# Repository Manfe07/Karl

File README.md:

# Karl
ROS based Raspberry Pi Robot with LIDAR

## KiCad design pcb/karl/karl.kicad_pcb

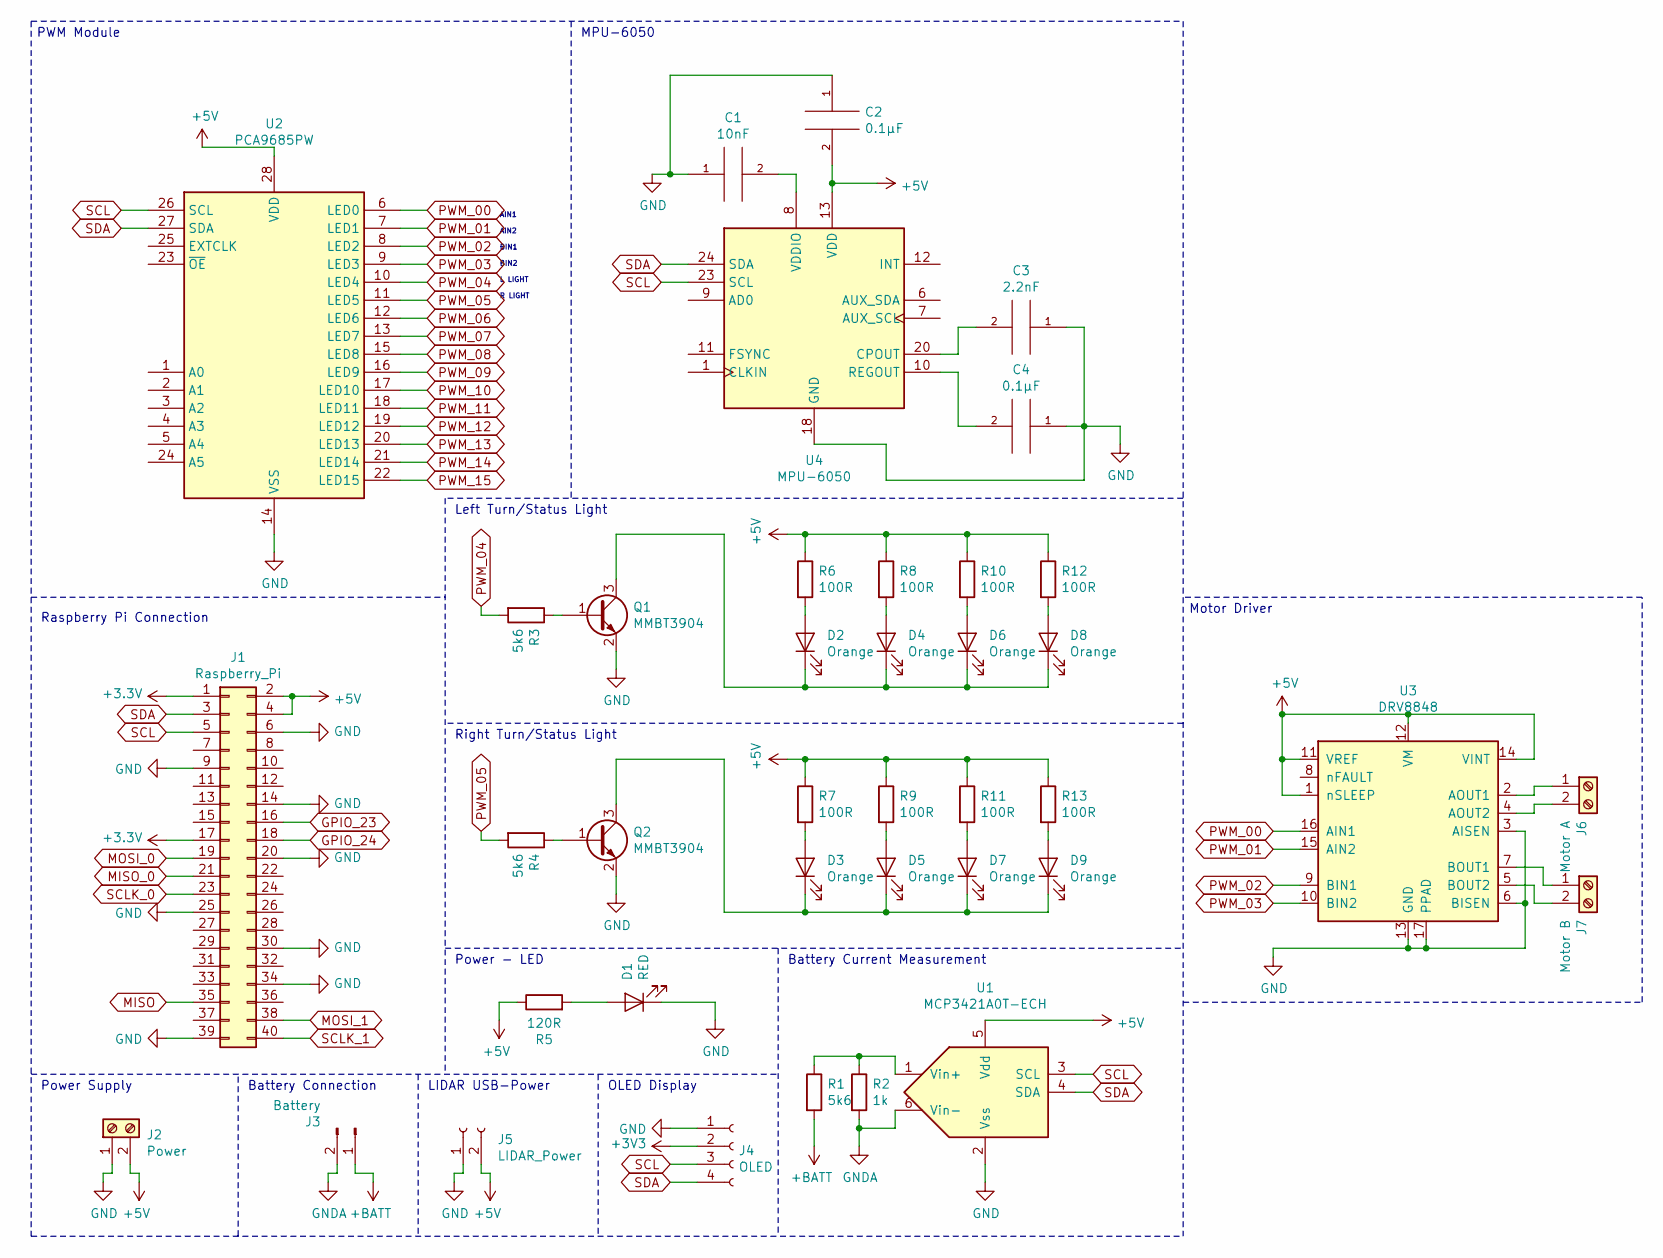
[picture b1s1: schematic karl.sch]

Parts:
C1: 10nF; C_0201_0603Metric
C2, C4: 0.1µF; C_0201_0603Metric
C3: 2.2nF; C_0201_0603Metric
D1: RED; LED_0603_1608Metric; LCSC C72044
D2, D3, D4, D5, D6, D7, D8, D9: Orange; LED_0603_1608Metric; LCSC C205445
J1: Raspberry_Pi; PinHeader_2x20_P2.54mm_Vertical
J2: Power; TerminalBlock_bornier-2_P5.08mm
J3: Battery; PinHeader_1x02_P2.54mm_Vertical
J4: OLED; PinHeader_1x04_P2.54mm_Vertical
J5: LIDAR_Power; PinSocket_1x02_P2.54mm_Vertical
J6: Motor A; TerminalBlock_bornier-2_P5.08mm
J7: Motor B; TerminalBlock_bornier-2_P5.08mm
Q1, Q2: MMBT3904; SOT-23; LCSC C181119
R1, R3, R4: 5k6; R_0603_1608Metric; LCSC C179095
R2: 1k; R_0603_1608Metric; LCSC C304078
R5: 120R; R_0603_1608Metric; LCSC C217712
R6, R7, R8, R9, R10, R11, R12, R13: 100R; R_0603_1608Metric; LCSC C217683
U1: MCP3421A0T-ECH; SOT-23-6; LCSC C29454
U2: PCA9685PW; TSSOP-28_4.4x9.7mm_P0.65mm; LCSC C110795
U3: DRV8848; TSSOP-16-1EP_4.4x5mm_P0.65mm; LCSC C131079
U4: MPU-6050; InvenSense_QFN-24_4x4mm_P0.5mm; LCSC C24112

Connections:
+5V: C2.2, J1.2, J1.4, J2.2, J5.2, R5.1, R6.1, R7.1, R8.1, R9.1, R10.1, R11.1, R12.1, R13.1, U1.5 (Vdd), U2.28 (VDD), U3.1 (nSLEEP), U3.11 (VREF), U3.12 (VM), U3.14 (VINT), U4.13 (VDD)
+BATT: J3.1, R1.2
GND: C1.1, C2.1, C3.1, C4.1, D1.1 (K), J1.6, J1.9, J1.14, J1.20, J1.25, J1.30, J1.34, J1.39, J2.1, J4.1, J5.1, Q1.2 (E), Q2.2 (E), U1.2 (Vss), U2.14 (VSS), U3.3 (AISEN), U3.6 (BISEN), U3.13 (GND), U3.17 (PPAD), U4.18 (GND)
GNDA: J3.2, R2.2, U1.6 (Vin-)
GPIO_23: J1.16
GPIO_24: J1.18
MISO: J1.35
MISO_0: J1.21
MOSI_0: J1.19
MOSI_1: J1.38
unnamed: C1.2, U4.8 (VDDIO)
unnamed: C3.2, U4.20 (CPOUT)
unnamed: C4.2, U4.10 (REGOUT)
unnamed: D1.2 (A), R5.2
unnamed: D2.1 (K), D4.1 (K), D6.1 (K), D8.1 (K), Q1.3 (C)
unnamed: D2.2 (A), R6.2
unnamed: D3.1 (K), D5.1 (K), D7.1 (K), D9.1 (K), Q2.3 (C)
unnamed: D3.2 (A), R7.2
unnamed: D4.2 (A), R8.2
unnamed: D5.2 (A), R9.2
unnamed: D6.2 (A), R10.2
unnamed: D7.2 (A), R11.2
unnamed: D8.2 (A), R12.2
unnamed: D9.2 (A), R13.2
unnamed: J6.1, U3.2 (AOUT1)
unnamed: J6.2, U3.4 (AOUT2)
unnamed: J7.1, U3.7 (BOUT1)
unnamed: J7.2, U3.5 (BOUT2)
unnamed: Q1.1 (B), R3.1
unnamed: Q2.1 (B), R4.1
unnamed: R1.1, R2.1, U1.1 (Vin+)
PWM_00: U2.6 (LED0), U3.16 (AIN1)
PWM_01: U2.7 (LED1), U3.15 (AIN2)
PWM_02: U2.8 (LED2), U3.9 (BIN1)
PWM_03: U2.9 (LED3), U3.10 (BIN2)
PWM_04: R3.2, U2.10 (LED4)
PWM_05: R4.2, U2.11 (LED5)
PWM_06: U2.12 (LED6)
PWM_07: U2.13 (LED7)
PWM_08: U2.15 (LED8)
PWM_09: U2.16 (LED9)
PWM_10: U2.17 (LED10)
PWM_11: U2.18 (LED11)
PWM_12: U2.19 (LED12)
PWM_13: U2.20 (LED13)
PWM_14: U2.21 (LED14)
PWM_15: U2.22 (LED15)
SCL: J1.5, J4.3, U1.3 (SCL), U2.26 (SCL), U4.23 (SCL)
SCLK_0: J1.23
SCLK_1: J1.40
SDA: J1.3, J4.4, U1.4 (SDA), U2.27 (SDA), U4.24 (SDA)

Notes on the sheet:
Power Supply
Battery Connection
Raspberry Pi Connection
LIDAR USB-Power
Battery Current Measurement
Power - LED
Right Turn/Status Light
Left Turn/Status Light
PWM Module
AIN1 AIN2 BIN1 BIN2 L LIGHT R LIGHT
Motor Driver
OLED Display
MPU-6050

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
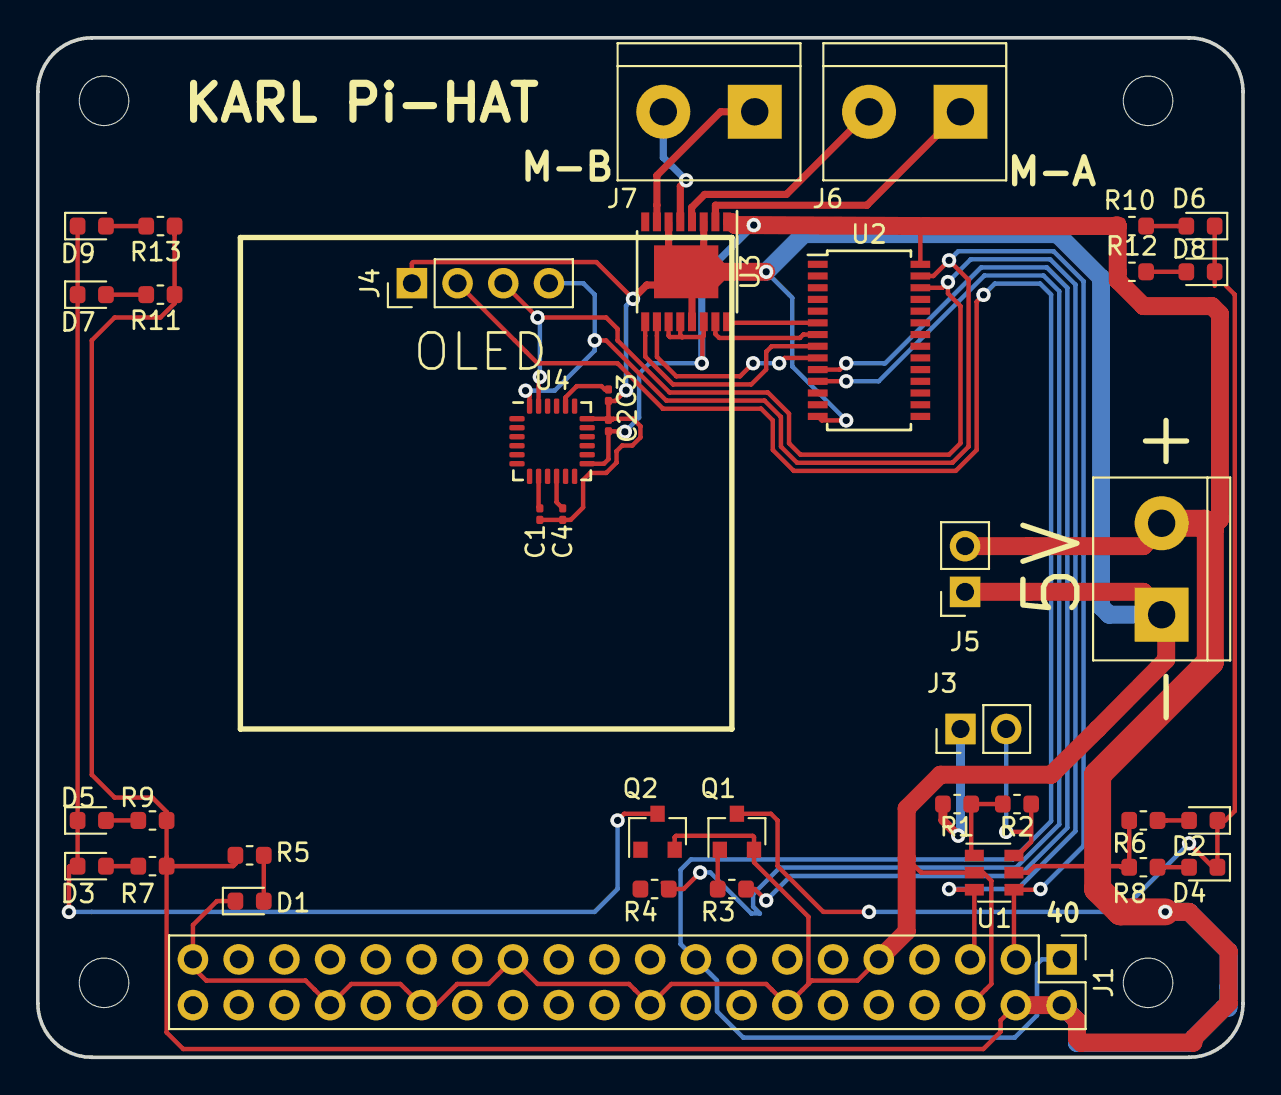
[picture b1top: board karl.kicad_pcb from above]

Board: 2 copper layers, 67.0 x 56.6 mm, 43 parts (0 on the bottom side), 34 nets.

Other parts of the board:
H1, H2, H5, H6: MountingHole; MountingHole_2.75mm_NoPad

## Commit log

2020-02-18 added custom launchfiles
    created custom launchfiles
2020-02-18 created ROS-Package
2020-02-18 added Visual Studio Code to .gitignore
2020-02-18 created rviz config file
2020-02-18 added rviz config file to launch file
2020-02-21 added python test script
2020-02-21 updated .gitignore
2020-02-21 changed python test
2020-02-21 added H-Driver files
2020-02-21 changes on driver
2020-02-21 minor changes at driver script
2020-02-21 working llc for motor
2020-02-23 updated launch files
2020-02-23 minor change in launch files
2020-02-26 updated urdf model
2020-02-28 updatet launch files
2020-03-03 added mapping to karl.launch
2020-03-03 nearly calibratet speed
2020-03-03 updated pc_server.launch
2020-03-03 created speed calculation
2020-03-07 first start
2020-03-07 project saved
2020-03-07 added turning lights
2020-03-07 minor changes
2020-03-07 saved
2020-03-07 try to fix
2020-03-07 changes screw terminal
2020-03-08 added pwm an motor module
2020-03-09 added Pi Hat layout and OLED display
2020-03-09 added MPU6050
2020-03-10 added speed calculation
2020-03-10 seperated yd-lidar launch file
2020-03-10 moved transformation to server
2020-03-10 moved gmapping to seperated launch file
2020-03-10 updated launch file
2020-03-10 changed motor input gain
2020-03-11 added amcl
2020-03-11 splitt launch files
2020-03-11 fixed error
2020-03-11 fixed launchfile error
2020-03-11 added maps folder to .gitignore
